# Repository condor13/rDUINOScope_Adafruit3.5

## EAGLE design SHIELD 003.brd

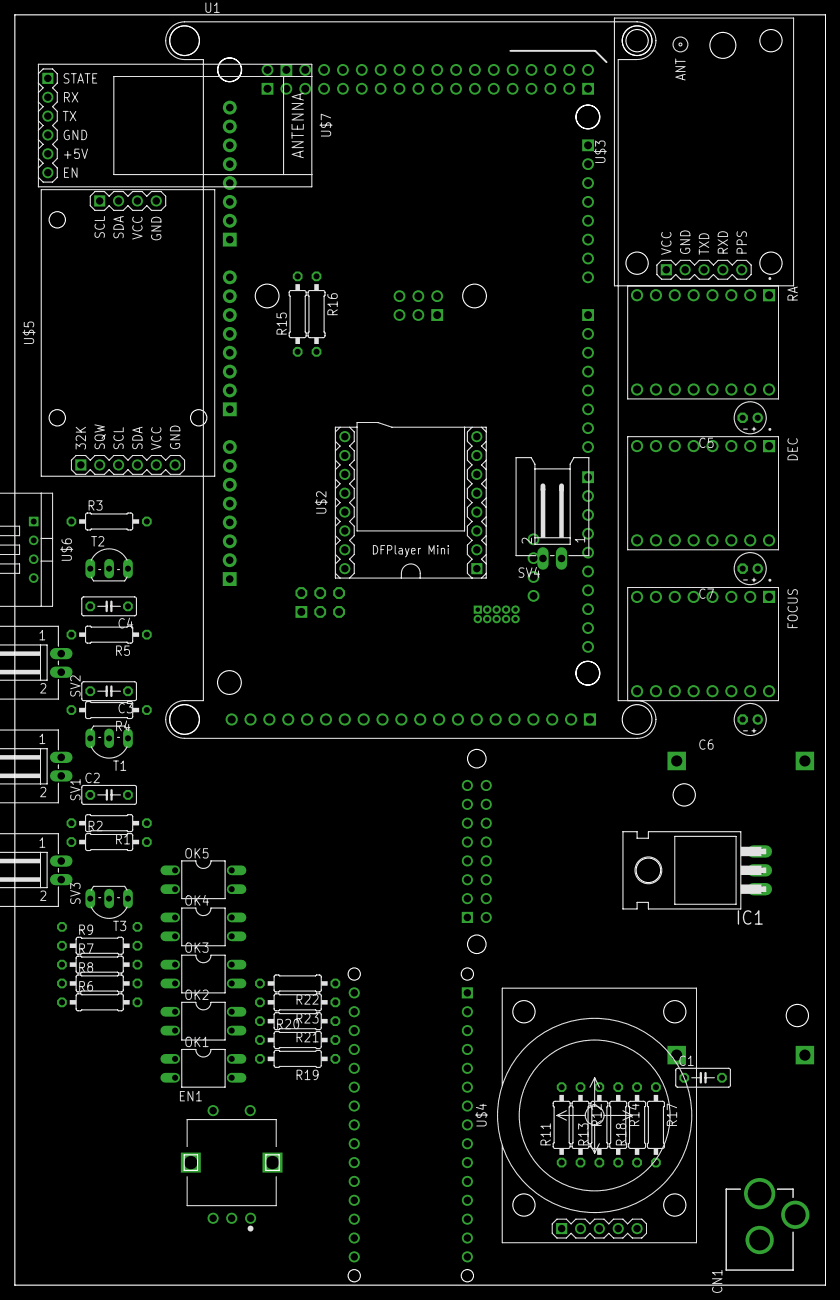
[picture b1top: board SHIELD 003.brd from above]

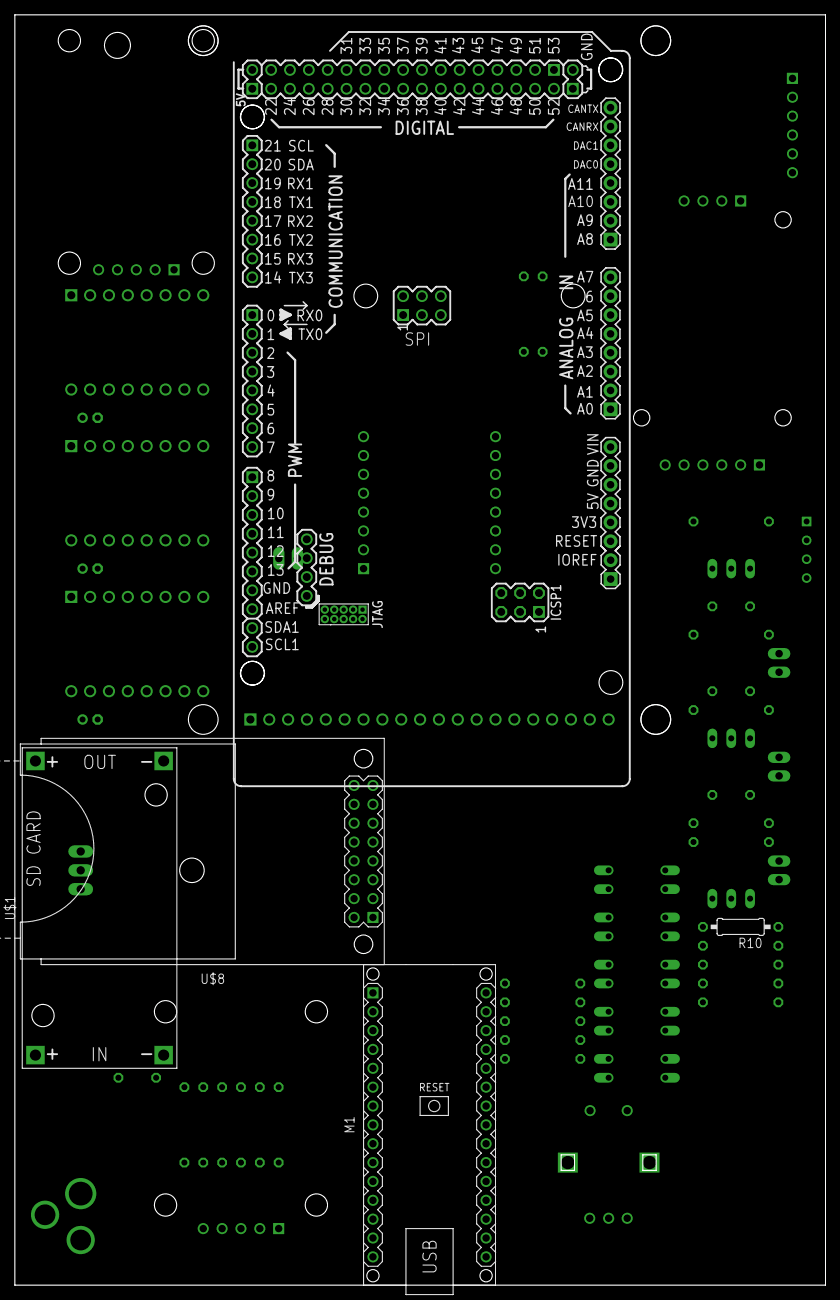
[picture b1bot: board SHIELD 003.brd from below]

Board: 2 copper layers, 109.2 x 171.1 mm, 59 parts (5 on the bottom side), 65 nets, no tracks yet.

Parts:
ARDUINO_DUE1: ARDUINO_DUE_SHIELD
C1: 10uF; C050-025X075
C2: 100nF; C050-025X075
C3, C4: C050-025X075
C5, C6, C7: 100uF; E2-4
CN1: DCJACK_2MM_PTH
DEC: DRV8825_STEPPER_MOTOR_DRIVER_CARRIER; IC_DRV8825_STEPPER_MOTOR_DRIVER_CARRIER
EN1: EVE-WRHJR012B
FOCUS: DRV8825_STEPPER_MOTOR_DRIVER_CARRIER; IC_DRV8825_STEPPER_MOTOR_DRIVER_CARRIER
IC1: 7805T; TO220H
M1: ARDUINO-NANO-3.0
OK1, OK2, OK3, OK4, OK5: PC817; DIL04
R1: 220; 0207/10
R2: 6.8; 0207/10
R3: 10K; 0207/10
R4, R5: 330; 0207/10
R6, R7, R8, R9, R10, R19, R20, R21, R22, R23: 100; 0207/10
R11, R13, R18: 100k; 0207/10
R12, R14, R17: 47k; 0207/10
R15: 10k; 0207/10
R16: 26k; 0207/10
RA: DRV8825_STEPPER_MOTOR_DRIVER_CARRIER; IC_DRV8825_STEPPER_MOTOR_DRIVER_CARRIER
SV1, SV2, SV3, SV4: L02P
T1, T2, T3: 2N2222; TO92-EBC-OVAL
U1: 3.5INCH
U$1: DC-DC-STEP-DOWN-LM2596
U$2: DFPLAYER-MINI-MODULE
U$3: GPS-RECEIVER-NEO6M
U$4: JOYSTICK-2AXIS-BUTTON
U$5: RTC-DS3231-AT24C32
U$6: TEMP-HUM-SENSOR-DHT22
U$7: WIRELESS-BLUETOOTH-HC-05
U$8: CARD-SD-ADAPTER

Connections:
3V3: ARDUINO_DUE1.3V3, DEC.5, DEC.6, DEC.10, FOCUS.5, FOCUS.6, FOCUS.10, M1.J2.14, OK1.3, OK2.3, OK3.3, OK4.3, OK5.3, R3.1, RA.5, RA.6, RA.10, U$6.1, U$8.3
5V: R2.2, SV1.2, SV2.2, U$1.OUT+, U$2.1, U$5.J1.5, U$7.5, U$8.5
5V_A: ARDUINO_DUE1.5V0, ARDUINO_DUE1.5V0_1, ARDUINO_DUE1.5V0_2, M1.J2.4, U$3.1, U$4.2
9V: ARDUINO_DUE1.VIN, C2.1, IC1.3, M1.J2.1
12V: C1.1, C5.+, C6.+, C7.+, CN1.PWR, DEC.16, FOCUS.16, IC1.1, R16.2, RA.16, U$1.IN+
DAC1: ARDUINO_DUE1.DAC1, R1.1
DEC+: M1.J1.9, R8.1
DEC-: M1.J1.6, R9.1
DEC_M0: ARDUINO_DUE1.10, DEC.2
DEC_M1: ARDUINO_DUE1.9, DEC.3
DEC_M2: ARDUINO_DUE1.8, DEC.4
G-SENSE: M1.J1.10, R10.1
GND: ARDUINO_DUE1.GND, ARDUINO_DUE1.GND_1, ARDUINO_DUE1.GND_2, ARDUINO_DUE1.GND_3, ARDUINO_DUE1.GND_4, ARDUINO_DUE1.GND_5, ARDUINO_DUE1.GND_7, ARDUINO_DUE1.GND_8, ARDUINO_DUE1.GND_9, ARDUINO_DUE1.GND_10, C1.2, C2.2, C3.2, C4.2, C5.-, C6.-, C7.-, CN1.GND, DEC.9, DEC.15, FOCUS.9, FOCUS.15, IC1.2, M1.J1.4, M1.J2.2, OK1.2, OK2.2, OK3.2, OK4.2, OK5.2, R11.1, R13.1, R15.1, R18.1, RA.9, RA.15, T1.E, T2.E, T3.E, U1.GND, U$1.IN-, U$1.OUT-, U$2.7, U$2.10, U$3.2, U$4.1, U$5.J1.6, U$5.J2.4, U$6.4, U$7.4, U$8.1, U$8.15
unnamed: R1.2, T3.B
unnamed: R2.1, SV3.1
unnamed: SV1.1, T1.C
unnamed: R4.2, T1.B
unnamed: SV3.2, T3.C
unnamed: R5.2, T2.B
unnamed: SV2.1, T2.C
unnamed: R17.2, U$4.5
unnamed: OK5.4, R23.2
unnamed: OK4.4, R22.2
unnamed: OK3.4, R21.2
unnamed: OK2.4, R20.2
unnamed: OK1.4, R19.2
unnamed: OK5.1, R10.2
unnamed: OK4.1, R9.2
unnamed: OK3.1, R8.2
unnamed: OK2.1, R7.2
unnamed: OK1.1, R6.2
unnamed: R12.2, U$4.3
unnamed: R14.2, U$4.4
P_4: ARDUINO_DUE1.4, RA.7
P_5: ARDUINO_DUE1.5, RA.8
P_6: ARDUINO_DUE1.6, DEC.7
P_7: ARDUINO_DUE1.7, DEC.8
P_14: ARDUINO_DUE1.14, U$7.2
P_15: ARDUINO_DUE1.15, U$7.3
P_16: ARDUINO_DUE1.16, U$3.4
P_17: ARDUINO_DUE1.17, U$3.3
P_18: ARDUINO_DUE1.18, U$2.2
P_19: ARDUINO_DUE1.19, U$2.3
P_21: ARDUINO_DUE1.21, U$8.7
P_27: ARDUINO_DUE1.27, FOCUS.8
P_29: ARDUINO_DUE1.29, FOCUS.7
P_43: ARDUINO_DUE1.43, R3.2, U$6.2
P_47: ARDUINO_DUE1.47, RA.1
P_49: ARDUINO_DUE1.49, DEC.1
P_51: ARDUINO_DUE1.51, FOCUS.1
P_A0: ARDUINO_DUE1.A0, R13.2, R14.1
P_A1: ARDUINO_DUE1.A1, R11.2, R12.1
P_A2: ARDUINO_DUE1.A2, C3.1, R4.1
P_A3: ARDUINO_DUE1.A3, C4.1, R5.1
P_A4: ARDUINO_DUE1.A4, U$5.J1.4
P_A5: ARDUINO_DUE1.A5, U$5.J1.3
P_A7: ARDUINO_DUE1.A7, R15.2, R16.1
P_A9: ARDUINO_DUE1.A9, R17.1, R18.2
RA+: M1.J1.7, R6.1
RA-: M1.J1.8, R7.1
RA_M0: ARDUINO_DUE1.11, RA.2
RA_M1: ARDUINO_DUE1.12, RA.3
RA_M2: ARDUINO_DUE1.13, RA.4
SPK1: SV4.2, U$2.8
SPK2: SV4.1, U$2.6

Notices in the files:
parts and their libraries:
diy-modules: Released under the Creative Commons Attribution 4.0 International License: http://creativecommons.org/licenses/by/4.0
